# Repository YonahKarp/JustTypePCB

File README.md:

PCB for the first prototype of the JustType Leaf [JustTypeLeaf.com](https://justtypeleaf.com/)

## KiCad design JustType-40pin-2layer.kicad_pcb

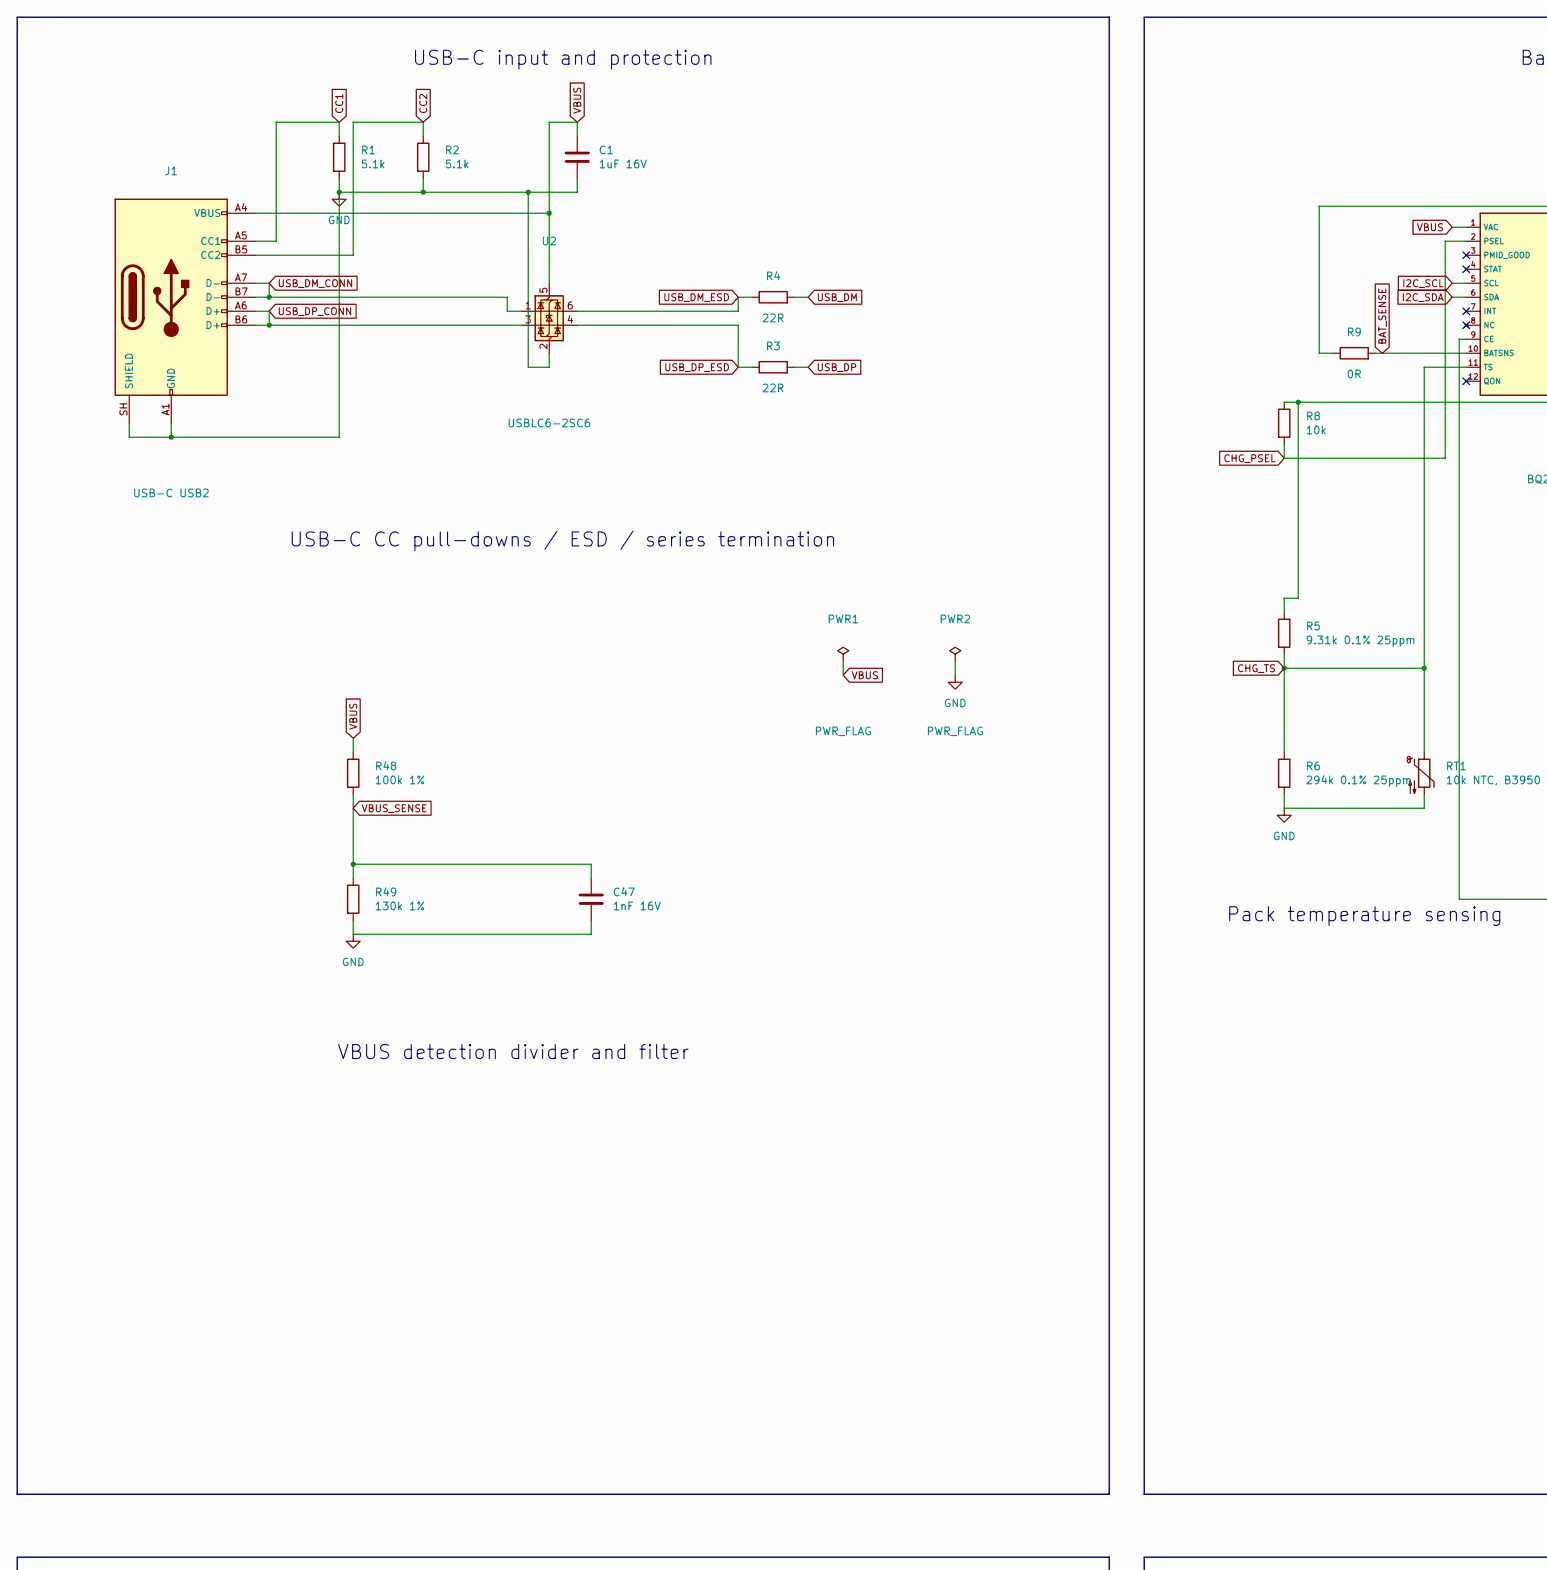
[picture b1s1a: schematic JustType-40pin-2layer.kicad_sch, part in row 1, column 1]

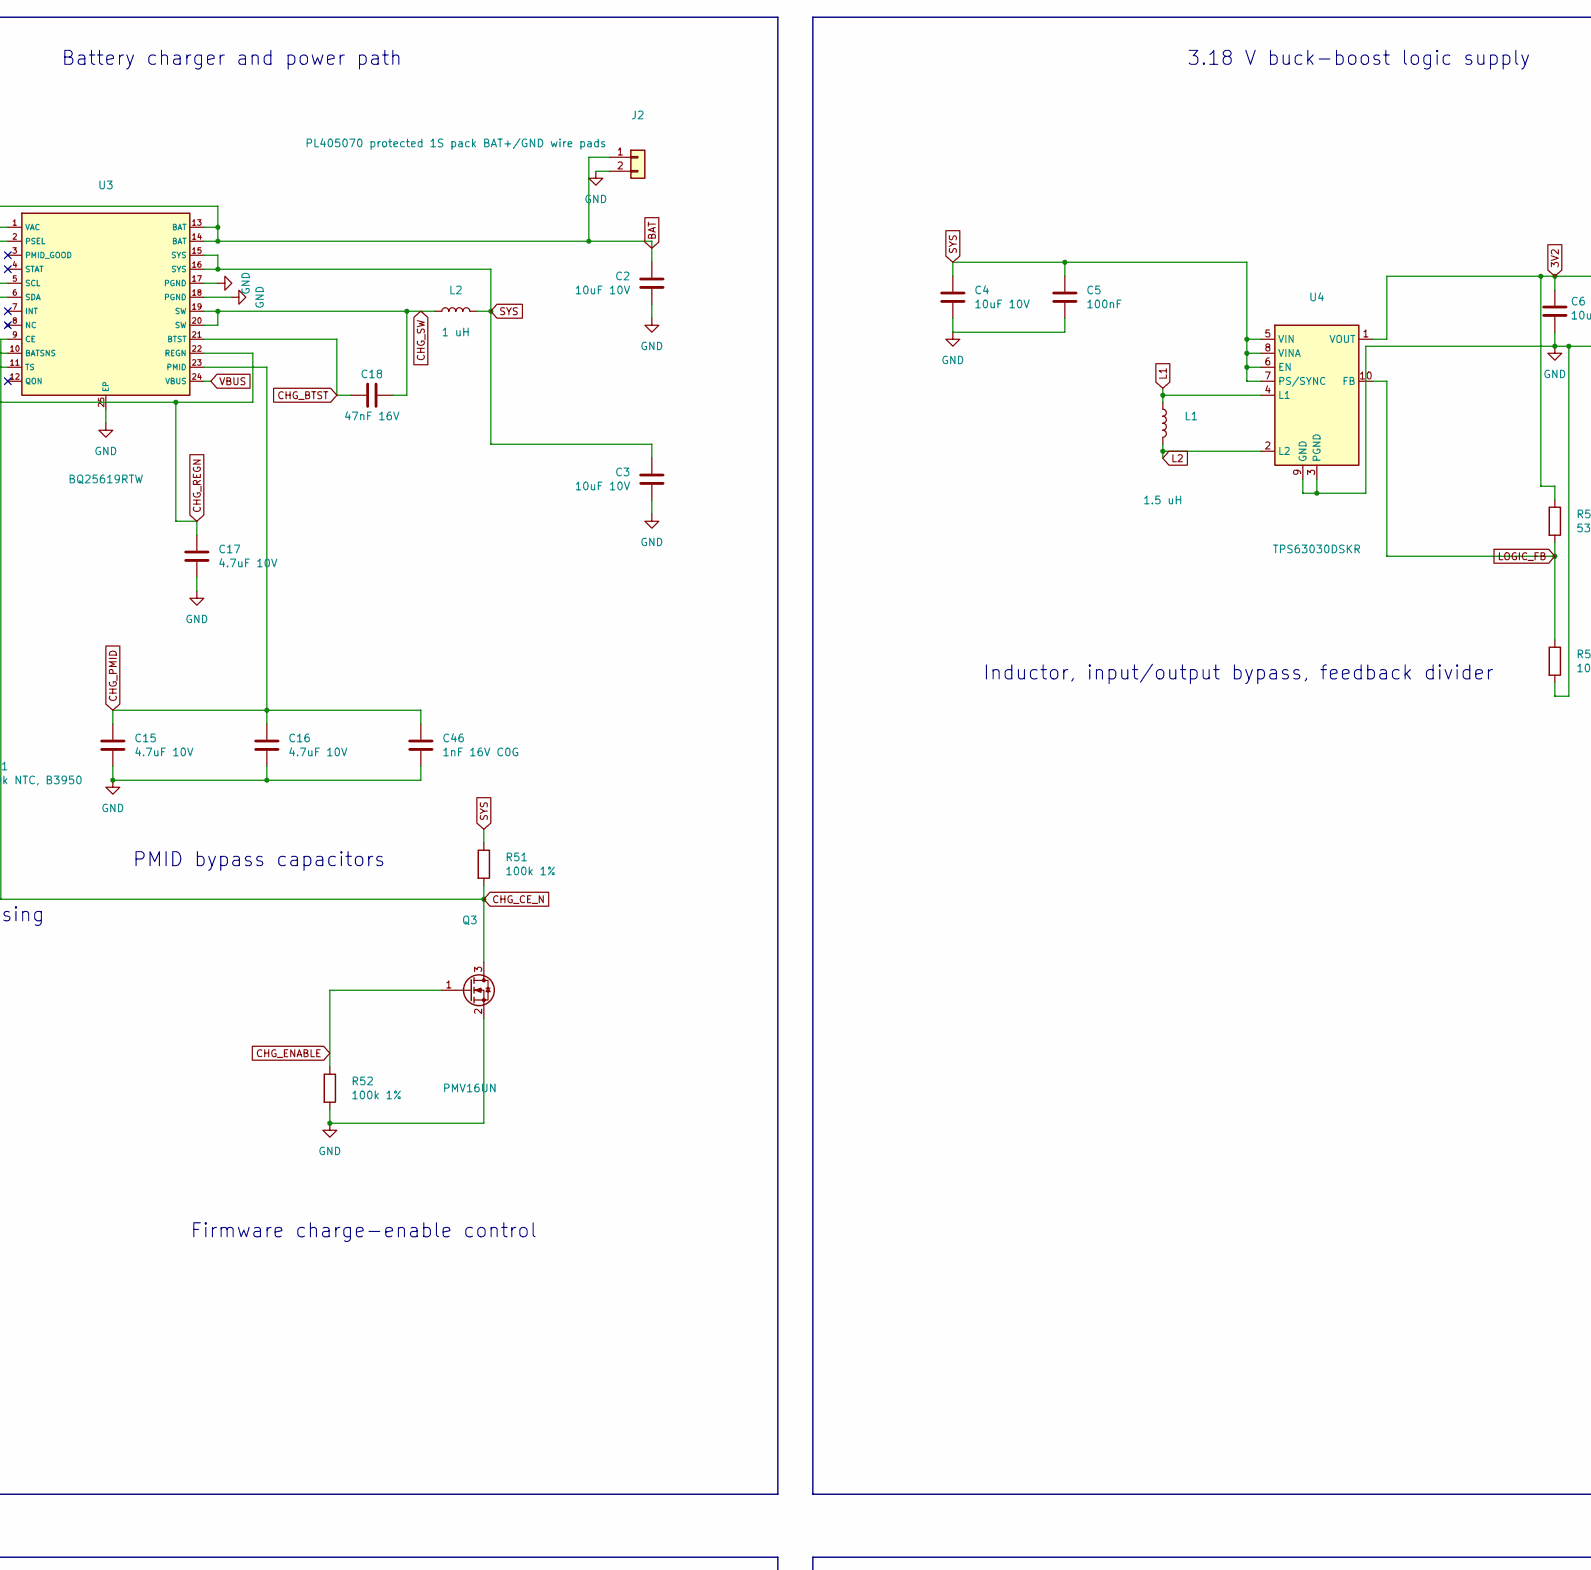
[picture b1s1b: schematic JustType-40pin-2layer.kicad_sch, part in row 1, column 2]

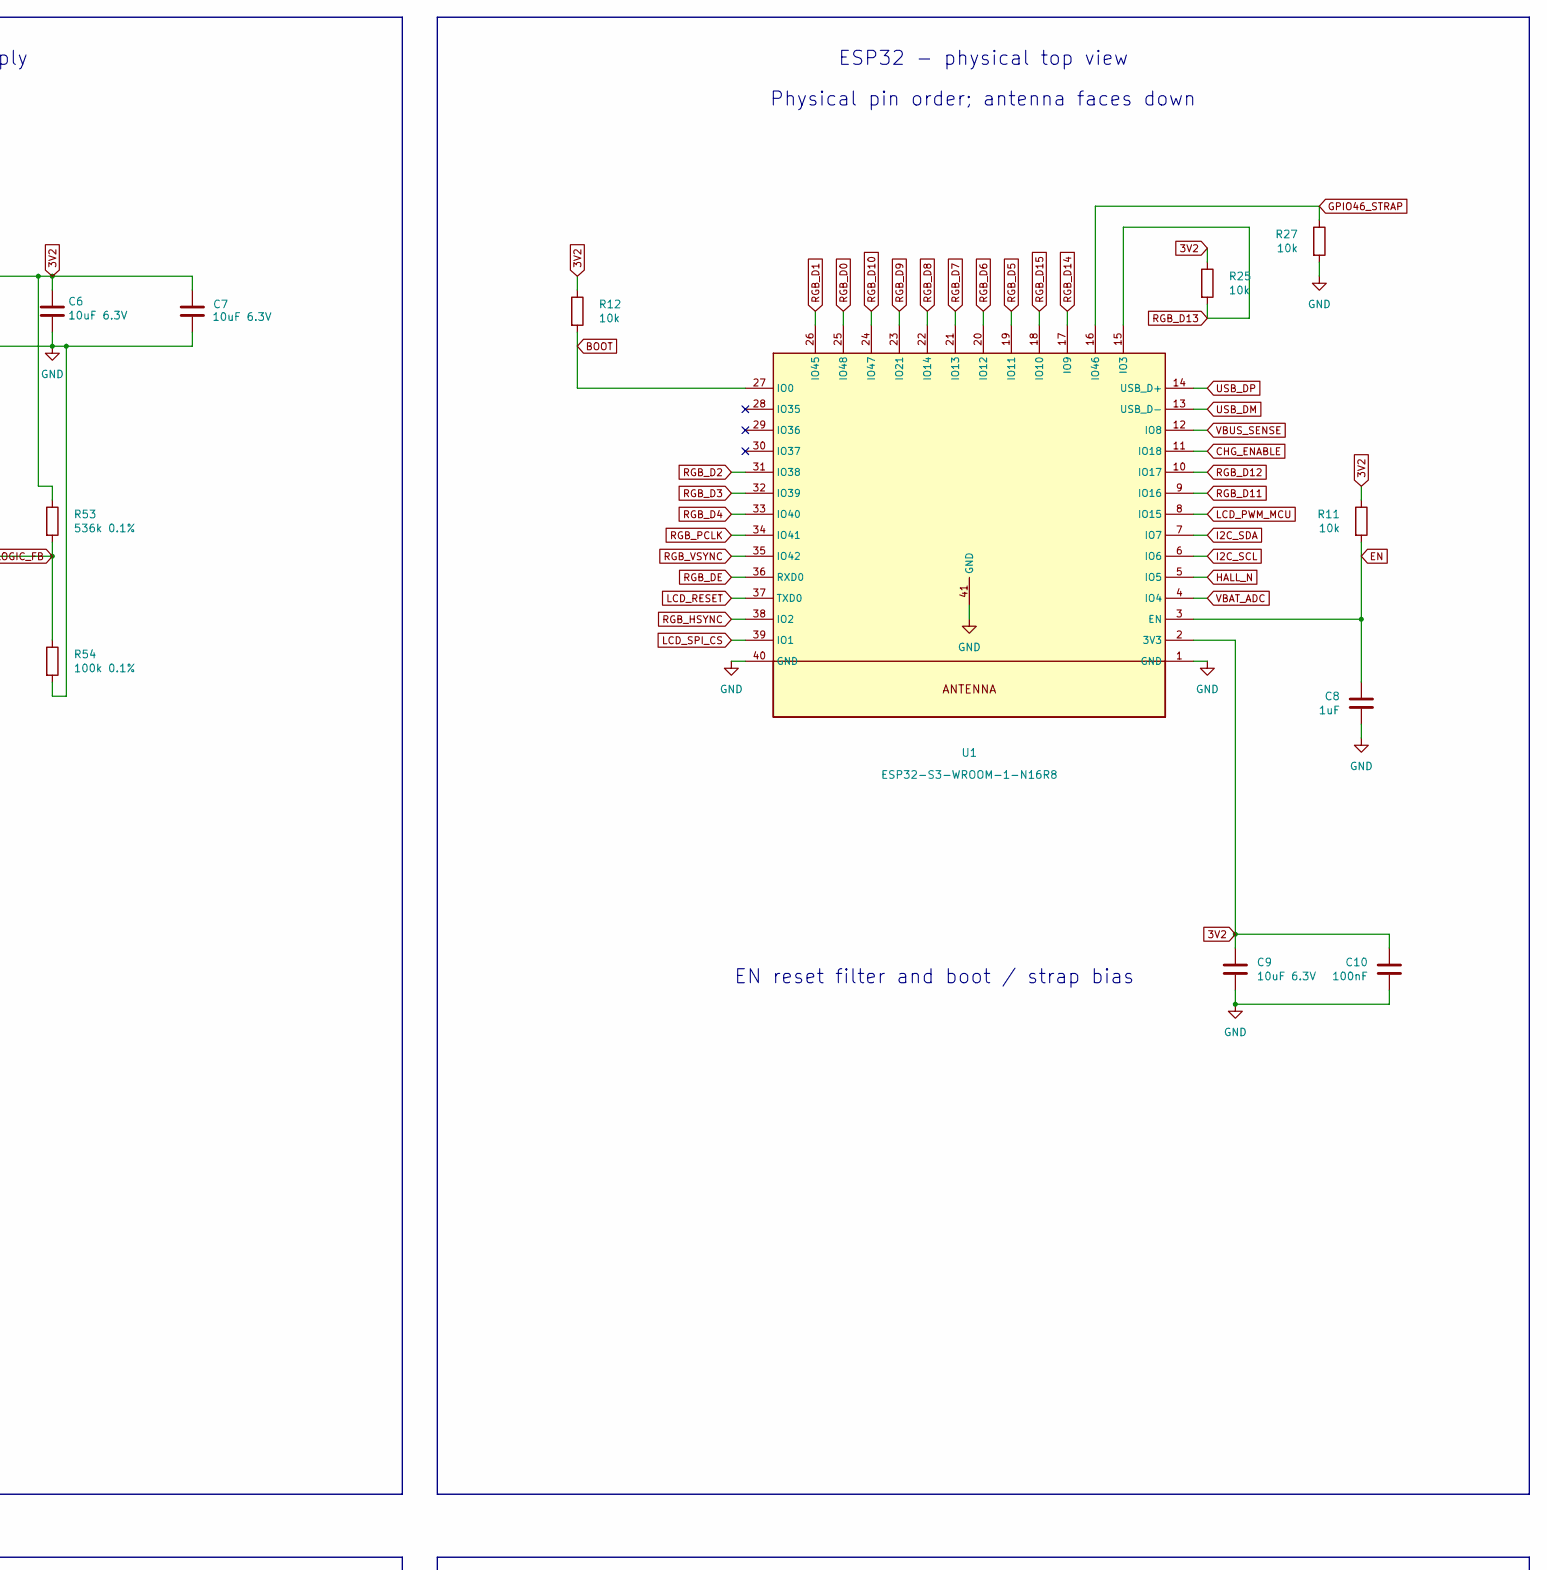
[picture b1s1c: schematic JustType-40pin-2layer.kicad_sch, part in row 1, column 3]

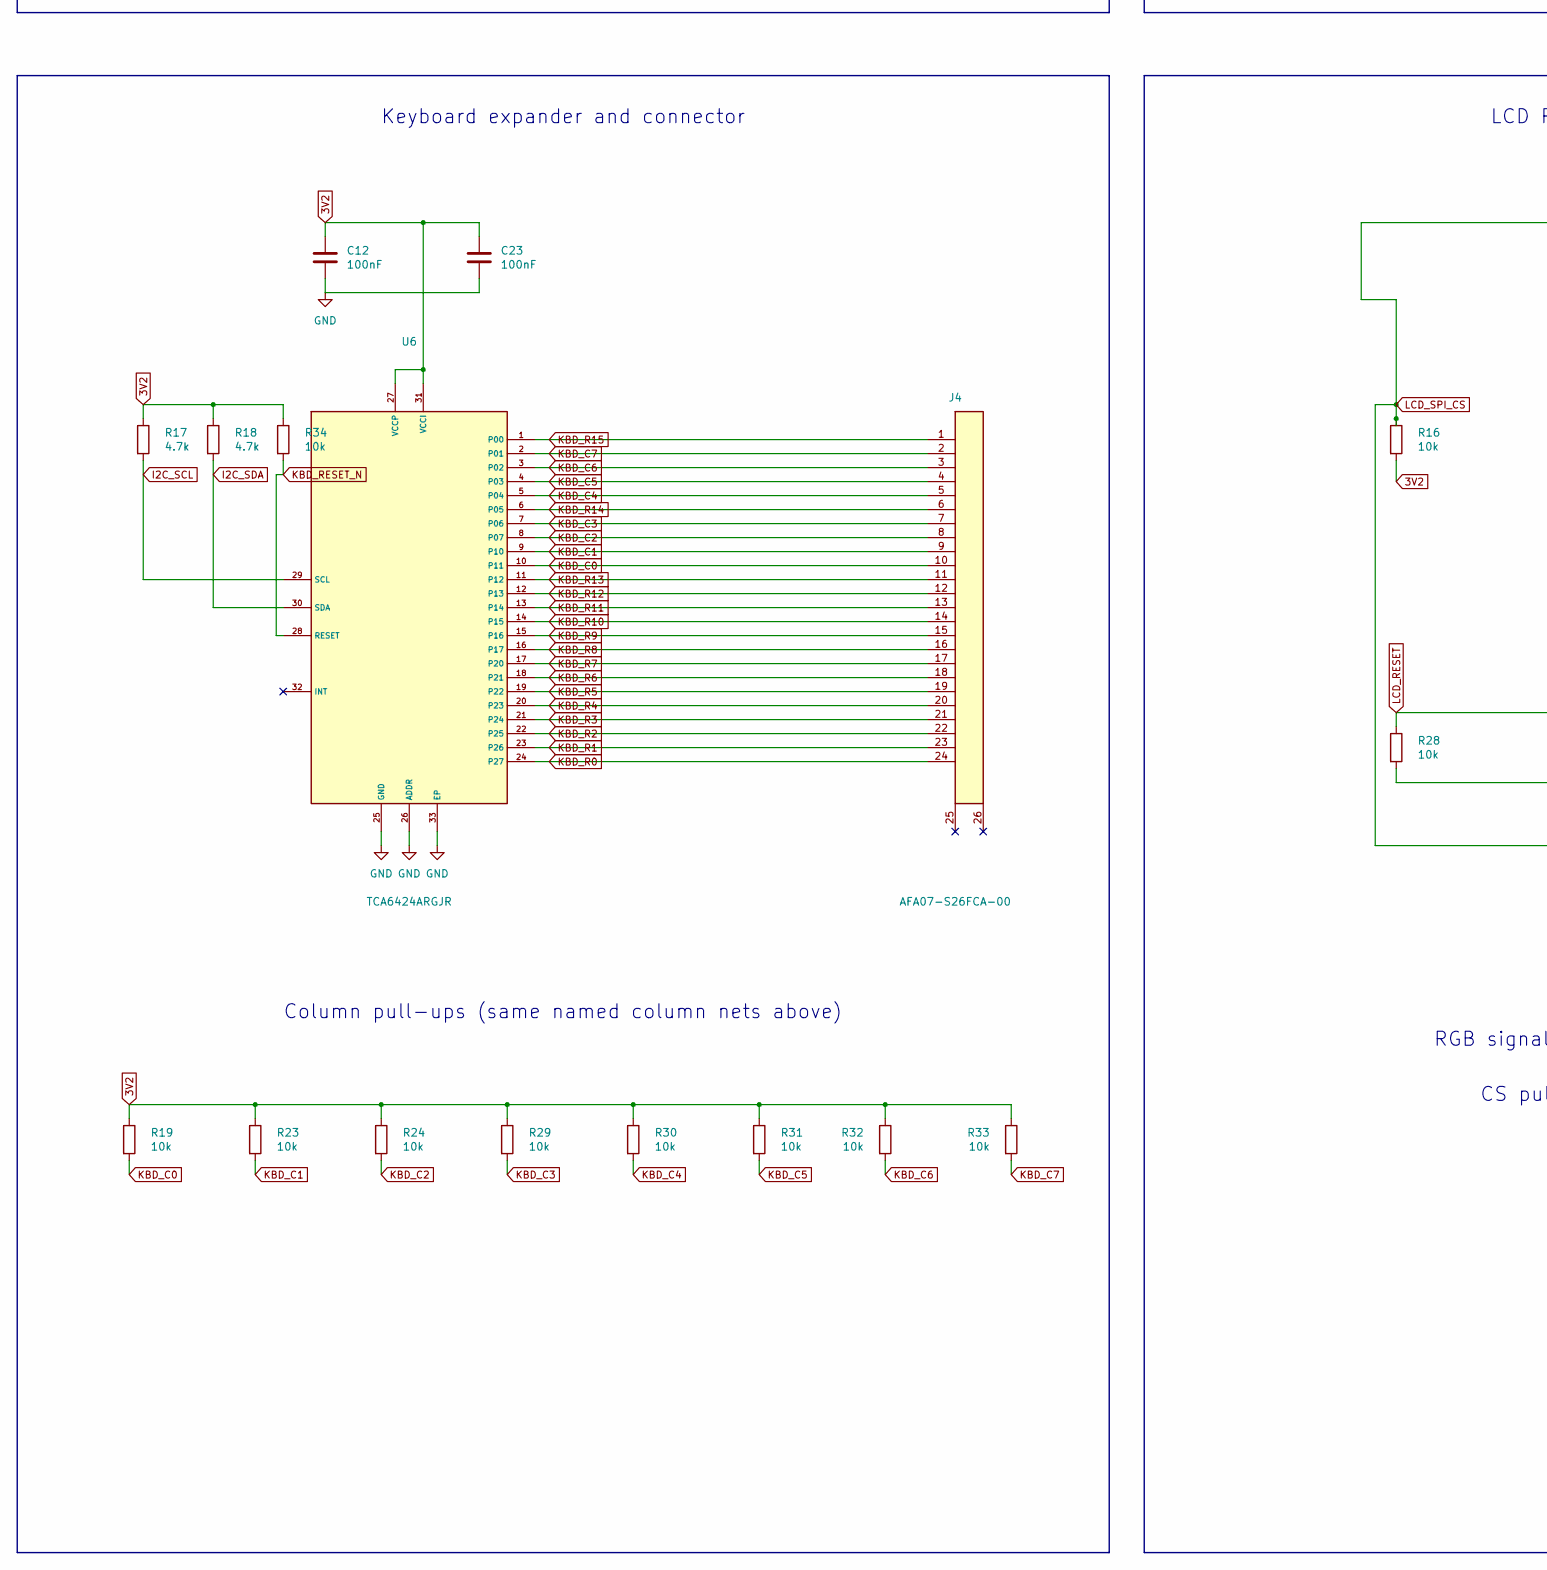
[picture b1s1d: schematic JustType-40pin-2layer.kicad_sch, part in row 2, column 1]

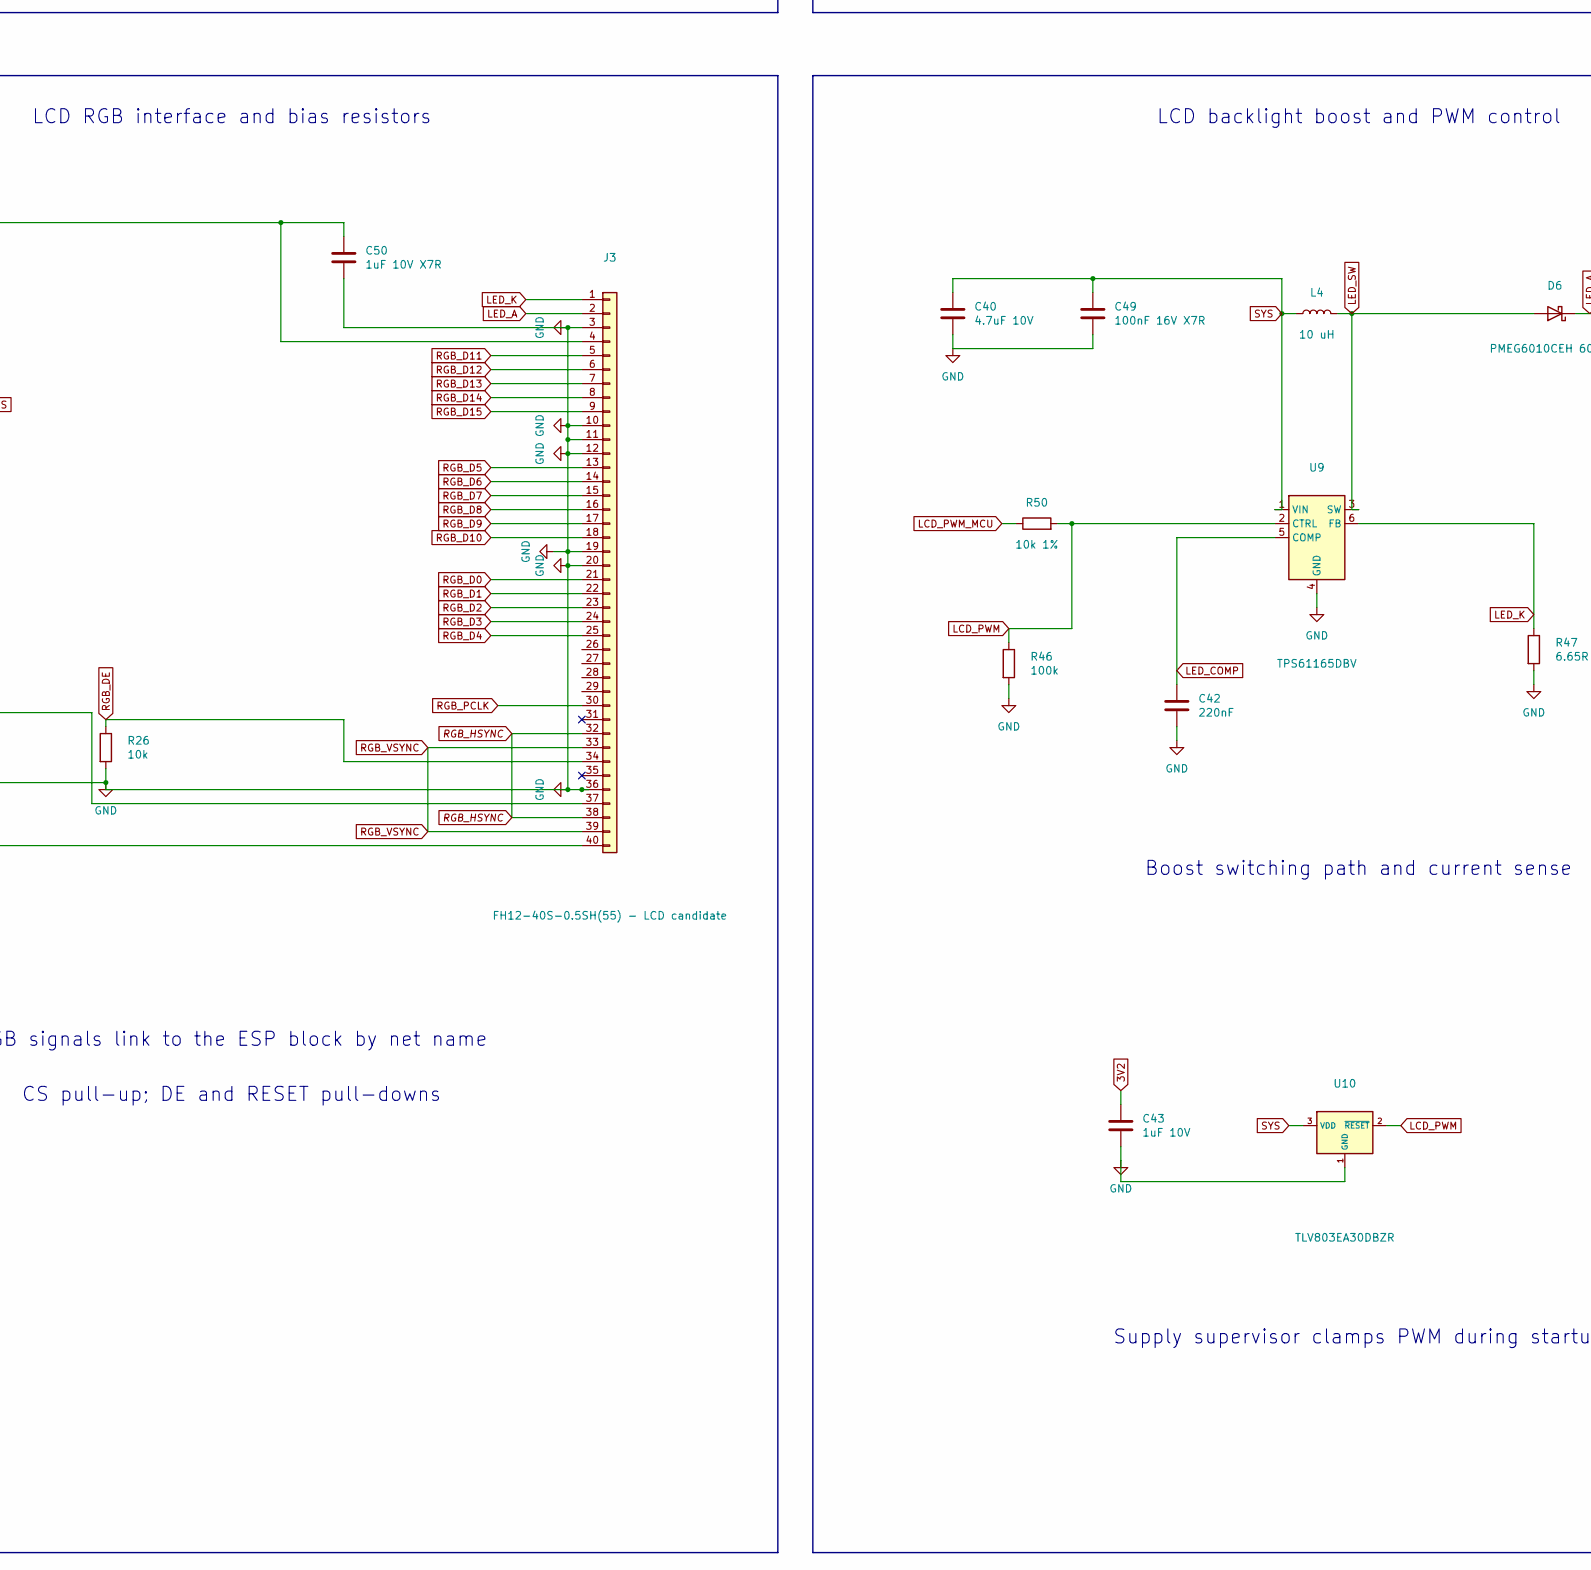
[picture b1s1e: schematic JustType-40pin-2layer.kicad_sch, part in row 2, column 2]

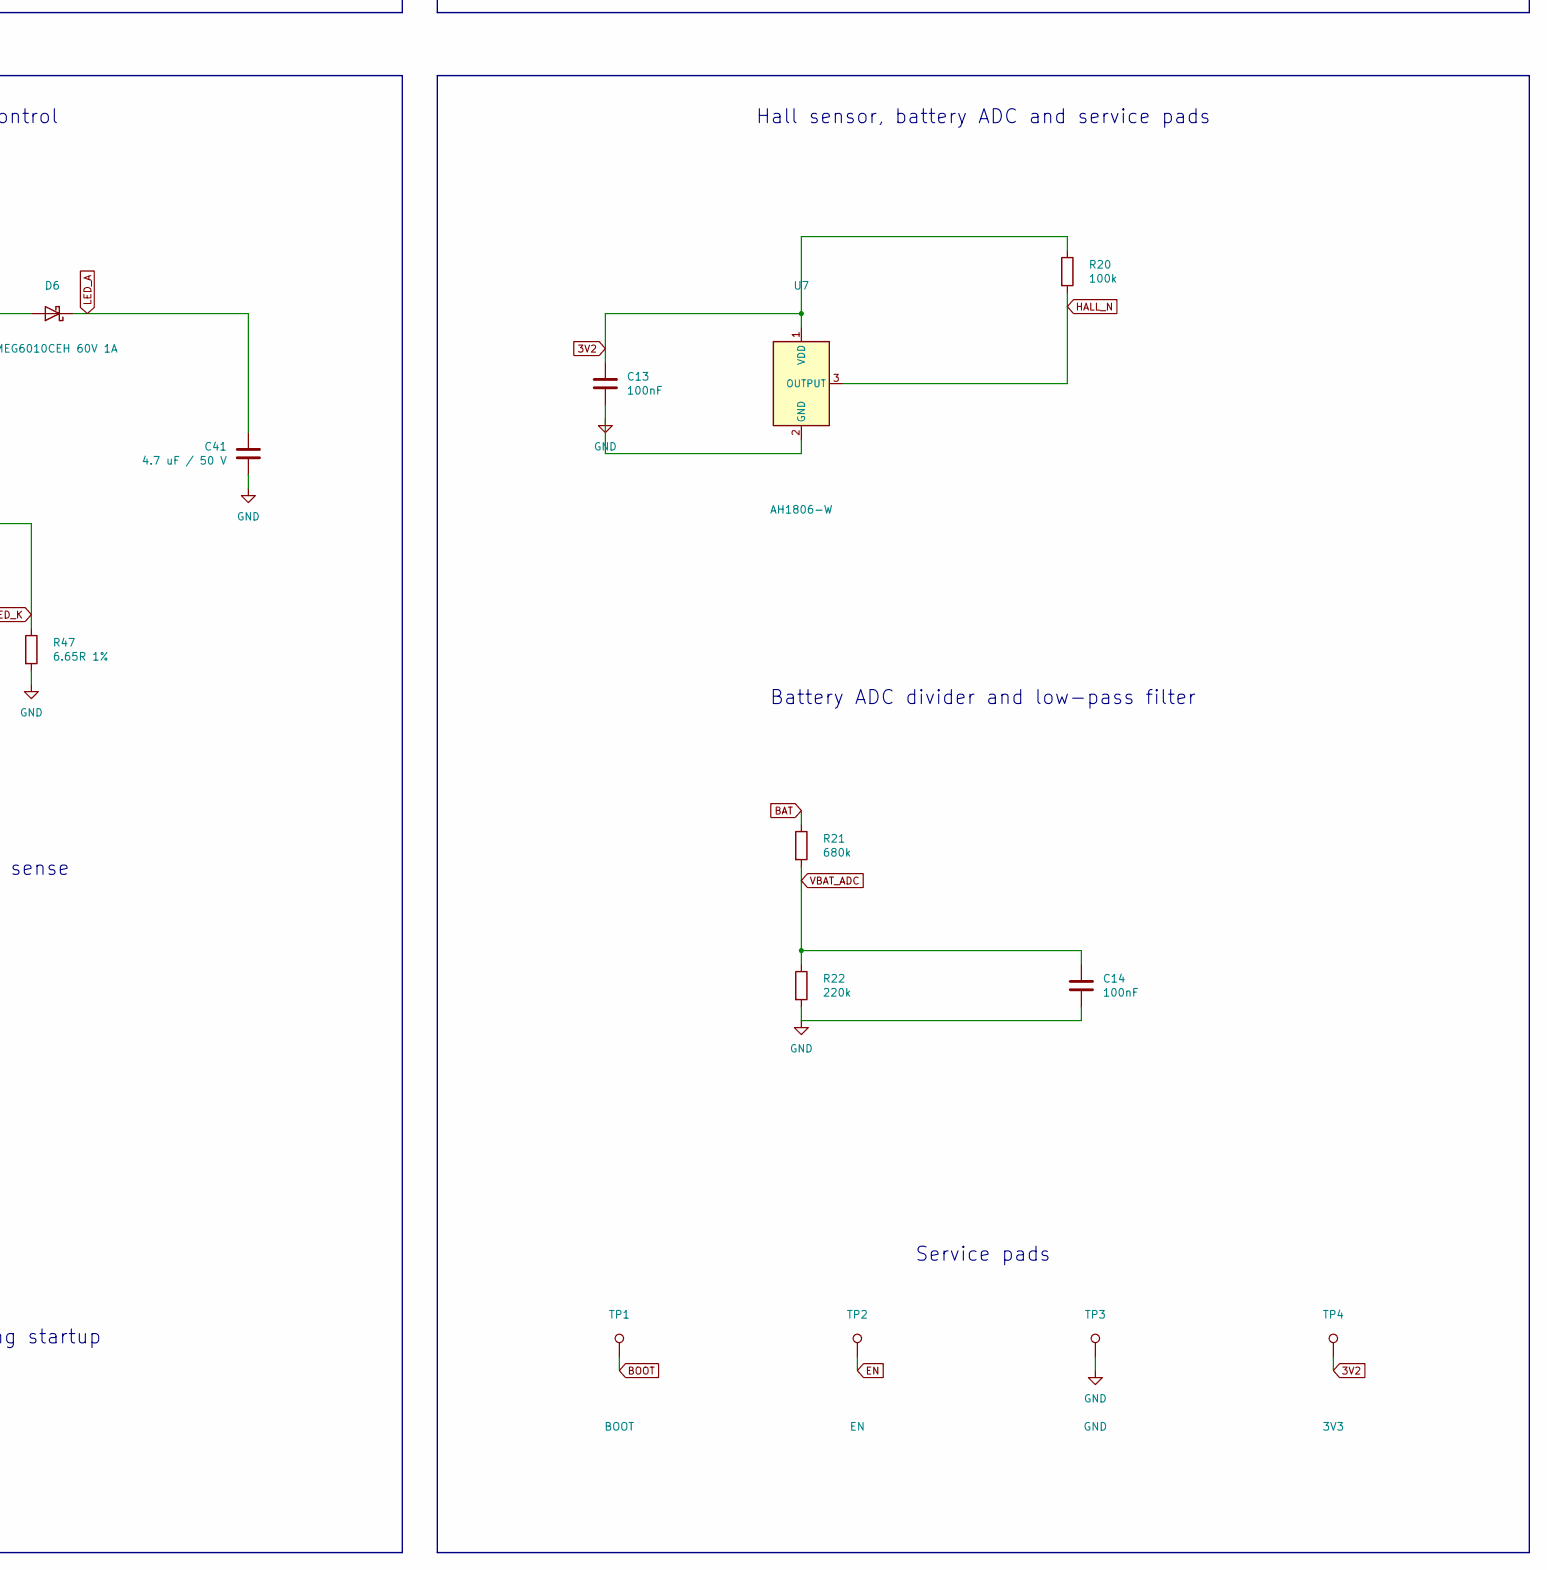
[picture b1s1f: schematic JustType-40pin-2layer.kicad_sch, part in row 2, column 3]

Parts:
C1: 1uF 16V; C_0402_1005Metric
C2, C3, C4: 10uF 10V; C_0805_2012Metric
C5, C10, C12, C13, C14, C23: 100nF; C_0603_1608Metric
C6, C7: 10uF 6.3V; C_0805_2012Metric
C8: 1uF; C_0603_1608Metric
C9: 10uF 6.3V; C_0603_1608Metric
C15, C16, C17, C40: 4.7uF 10V; C_0805_2012Metric
C18: 47nF 16V; C_0402_1005Metric
C41: 4.7uF 50V X7R GRM32ER71H475KA88K; C_1210_3225Metric
C42: 220nF; C_0603_1608Metric
C43: 1uF 10V; C_0603_1608Metric
C46: 1nF 16V C0G; C_0603_1608Metric
C47: 1nF 16V; C_0603_1608Metric
C49: 100nF 16V X7R; C_0402_1005Metric
C50: 1uF 10V X7R; C_0603_1608Metric
D6: PMEG6010CEH 60V 1A; D_SOD-123F
J1: USB-C USB2; USB_C_Receptacle_HRO_TYPE-C-31-M-12_Edge
J2: PL405070 protected 1S pack BAT+/GND wire pads; Battery_Wire_Solder_Pads
J3: FH12-40S-0.5SH(55) - LCD candidate; Hirose_FH12-40S-0.5SH_1x40-1MP_P0.50mm_Horizontal
J4: AFA07-S26FCA-00; JUSHUO_AFA07-S26FCA-00_1x26_P1.00mm_Horizontal
L1: SWPA3015S1R5NT 1.5uH; L_Sunlord_SWPA3015S
L2: SWPA3015S1R0NT 1uH; L_Sunlord_SWPA3015S
L4: SWPA4030S100MT 10uH; L_Sunlord_SWPA4030S
PWR1, PWR2: PWR_FLAG
Q3: PMV16UN; SOT-23
R1, R2: 5.1k; R_0603_1608Metric
R3, R4: 22R; R_0603_1608Metric
R5: 9.31k 0.1% 25ppm; R_0603_1608Metric
R6: 294k 0.1% 25ppm; R_0603_1608Metric
R8, R11, R12, R16, R19, R23, R24, R25, R26, R27, R28, R29, R30, R31, R32, R33, R34: 10k; R_0603_1608Metric
R9: 0R; R_0603_1608Metric
R17, R18: 4.7k; R_0603_1608Metric
R20, R46: 100k; R_0603_1608Metric
R21: 680k; R_0603_1608Metric
R22: 220k; R_0603_1608Metric
R47: 6.65R 1%; R_0603_1608Metric
R48, R51, R52: 100k 1%; R_0603_1608Metric
R49: 130k 1%; R_0603_1608Metric
R50: 10k 1%; R_0603_1608Metric
R53: 536k 0.1%; R_0603_1608Metric
R54: 100k 0.1%; R_0603_1608Metric
RT1: 10k NTC B3950 pack thermistor pads; Remote_NTC_Wire_Pads
TP1: BOOT; ServiceProbe_1mm_TP1
TP2: EN; ServiceProbe_1mm_TP2
TP3: GND; TestPoint_Pad_D1.5mm
TP4: 3V3; TestPoint_Pad_D1.5mm
U1: ESP32-S3-WROOM-1-N16R8; ESP32-S3-WROOM-1-NoRF
U2: USBLC6-2SC6; SOT-23-6
U3: BQ25619RTW; Texas_RTW_WQFN-24-1EP_4x4mm_P0.5mm_EP2.7x2.7mm
U4: TPS63030DSKR; WSON-10-1EP_2.5x2.5mm_P0.5mm_EP1.2x2mm
U6: TCA6424ARGJR; Texas_RGJ0032A_UQFN-32-1EP_5x5mm_P0.5mm_EP3.15x3.15mm
U7: AH1806-W; SC-59
U9: TPS61165DBV; SOT-23-6
U10: TLV803EA30DBZR; SOT-23

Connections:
BAT: C2.1, J2.1, R9.1, R21.1, U3.13 (BAT), U3.14 (BAT)
BAT_SENSE: R9.2, U3.10 (BATSNS)
BOOT: R12.2, TP1.1, U1.27 (IO0)
CC1: J1.A5 (CC1), R1.1
CC2: J1.B5 (CC2), R2.1
CHG_BTST: C18.1, U3.21 (BTST)
CHG_CE_N: Q3.3 (D), R51.2, U3.9 (CE)
CHG_ENABLE: Q3.1 (G), R52.1, U1.11 (IO18)
CHG_PMID: C15.1, C16.1, C46.1, U3.23 (PMID)
CHG_PSEL: R8.2, U3.2 (PSEL)
CHG_REGN: C17.1, R5.1, R8.1, U3.22 (REGN)
CHG_SW: C18.2, L2.1, U3.19 (SW), U3.20 (SW)
CHG_TS: R5.2, R6.1, RT1.1, U3.11 (TS)
EN: C8.1, R11.2, TP2.1, U1.3 (EN)
GND: C1.2, C2.2, C3.2, C4.2, C5.2, C6.2, C7.2, C8.2, C9.2, C10.2, C12.2, C13.2, C14.2, C15.2, C16.2, C17.2, C23.2, C40.2, C41.2, C42.2, C43.2, C46.2, C47.2, C49.2, C50.2, J1.A1 (GND), J1.A12 (GND), J1.B1 (GND), J1.B12 (GND), J1.SH (SHIELD), J2.2, J3.3, J3.10, J3.11, J3.12, J3.19, J3.20, J3.26, J3.27, J3.28, J3.29, J3.36, PWR2.1, Q3.2 (S), R1.2, R2.2, R6.2, R22.2, R26.2, R27.2, R28.2, R46.2, R47.2, R49.2, R52.2, R54.2, RT1.2, TP3.1, U1.1 (GND), U1.40 (GND), U1.41 (GND), U2.2 (GND), U3.17 (PGND), U3.18 (PGND), U3.25 (EP), U4.3 (PGND), U4.9 (GND), U4.11 (PGND), U6.25 (GND), U6.26 (ADDR), U6.33 (EP), U7.2 (GND), U9.4 (GND), U10.1 (GND)
GPIO46_STRAP: R27.1, U1.16 (IO46)
HALL_N: R20.2, U1.5 (IO5), U7.3 (OUTPUT)
I2C_SCL: R17.2, U1.6 (IO6), U3.5 (SCL), U6.29 (SCL)
I2C_SDA: R18.2, U1.7 (IO7), U3.6 (SDA), U6.30 (SDA)
KBD_C0: J4.10, R19.2, U6.10 (P11)
KBD_C1: J4.9, R23.2, U6.9 (P10)
KBD_C2: J4.8, R24.2, U6.8 (P07)
KBD_C3: J4.7, R29.2, U6.7 (P06)
KBD_C4: J4.5, R30.2, U6.5 (P04)
KBD_C5: J4.4, R31.2, U6.4 (P03)
KBD_C6: J4.3, R32.2, U6.3 (P02)
KBD_C7: J4.2, R33.2, U6.2 (P01)
KBD_R0: J4.24, U6.24 (P27)
KBD_R1: J4.23, U6.23 (P26)
KBD_R2: J4.22, U6.22 (P25)
KBD_R3: J4.21, U6.21 (P24)
KBD_R4: J4.20, U6.20 (P23)
KBD_R5: J4.19, U6.19 (P22)
KBD_R6: J4.18, U6.18 (P21)
KBD_R7: J4.17, U6.17 (P20)
KBD_R8: J4.16, U6.16 (P17)
KBD_R9: J4.15, U6.15 (P16)
KBD_R10: J4.14, U6.14 (P15)
KBD_R11: J4.13, U6.13 (P14)
KBD_R12: J4.12, U6.12 (P13)
KBD_R13: J4.11, U6.11 (P12)
KBD_R14: J4.6, U6.6 (P05)
KBD_R15: J4.1, U6.1 (P00)
KBD_RESET_N: R34.2, U6.28 (RESET)
L1: L1.1, U4.4 (L1)
L2: L1.2, U4.2 (L2)
LCD_PWM: R46.1, R50.2, U9.2 (CTRL), U10.2 (~RESET)
LCD_PWM_MCU: R50.1, U1.8 (IO15)
LCD_RESET: J3.37, R28.1, U1.37 (TXD0)
LED_A: C41.1, D6.1 (K), J3.2
LED_COMP: C42.1, U9.5 (COMP)
LED_K: J3.1, R47.1, U9.6 (FB)
LED_SW: D6.2 (A), L4.2, U9.3 (SW)
LOGIC_FB: R53.2, R54.1, U4.10 (FB)
RGB_D0: J3.21, U1.25 (IO48)
RGB_D1: J3.22, U1.26 (IO45)
RGB_D2: J3.23, U1.31 (IO38)
RGB_D3: J3.24, U1.32 (IO39)
RGB_D4: J3.25, U1.33 (IO40)
RGB_D5: J3.13, U1.19 (IO11)
RGB_D6: J3.14, U1.20 (IO12)
RGB_D7: J3.15, U1.21 (IO13)
RGB_D8: J3.16, U1.22 (IO14)
RGB_D9: J3.17, U1.23 (IO21)
RGB_D10: J3.18, U1.24 (IO47)
RGB_D11: J3.5, U1.9 (IO16)
RGB_D12: J3.6, U1.10 (IO17)
RGB_D13: J3.7, R25.2, U1.15 (IO3)
RGB_D14: J3.8, U1.17 (IO9)
RGB_D15: J3.9, U1.18 (IO10)
RGB_DE: J3.34, R26.1, U1.36 (RXD0)
RGB_HSYNC: J3.32, J3.38, U1.38 (IO2)
RGB_PCLK: J3.30, U1.34 (IO41)
RGB_VSYNC: J3.33, J3.39, U1.35 (IO42)
SYS: C3.1, C4.1, C5.1, C40.1, C49.1, L2.2, L4.1, R51.1, U3.15 (SYS), U3.16 (SYS), U4.5 (VIN), U4.6 (EN), U4.7 (PS/SYNC), U4.8 (VINA), U9.1 (VIN), U10.3 (VDD)
USB_DM: R4.2, U1.13 (USB_D-)
USB_DM_CONN: J1.A7 (D-), J1.B7 (D-), U2.1 (I/O1)
USB_DM_ESD: R4.1, U2.6 (I/O1)
USB_DP: R3.2, U1.14 (USB_D+)
USB_DP_CONN: J1.A6 (D+), J1.B6 (D+), U2.3 (I/O2)
USB_DP_ESD: R3.1, U2.4 (I/O2)
VBAT_ADC: C14.1, R21.2, R22.1, U1.4 (IO4)
VBUS: C1.1, J1.A4 (VBUS), J1.A9 (VBUS), J1.B4 (VBUS), J1.B9 (VBUS), PWR1.1, R48.1, U2.5 (VBUS), U3.1 (VAC), U3.24 (VBUS)
VBUS_SENSE: C47.1, R48.2, R49.1, U1.12 (IO8)

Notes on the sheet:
Battery ADC divider and low-pass filter
Physical pin order; antenna faces down
USB-C CC pull-downs / ESD / series termination
PMID bypass capacitors
Inductor, input/output bypass, feedback divider
Pack temperature sensing
3.18 V buck-boost logic supply
VBUS detection divider and filter
Battery charger and power path
Supply supervisor clamps PWM during startup
Boost switching path and current sense
Keyboard expander and connector
LCD RGB interface and bias resistors
USB-C input and protection
RGB signals link to the ESP block by net name
Column pull-ups (same named column nets above)
EN reset filter and boot / strap bias
LCD backlight boost and PWM control
ESP32 - physical top view
CS pull-up; DE and RESET pull-downs
Firmware charge-enable control
Service pads
Hall sensor, battery ADC and service pads

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
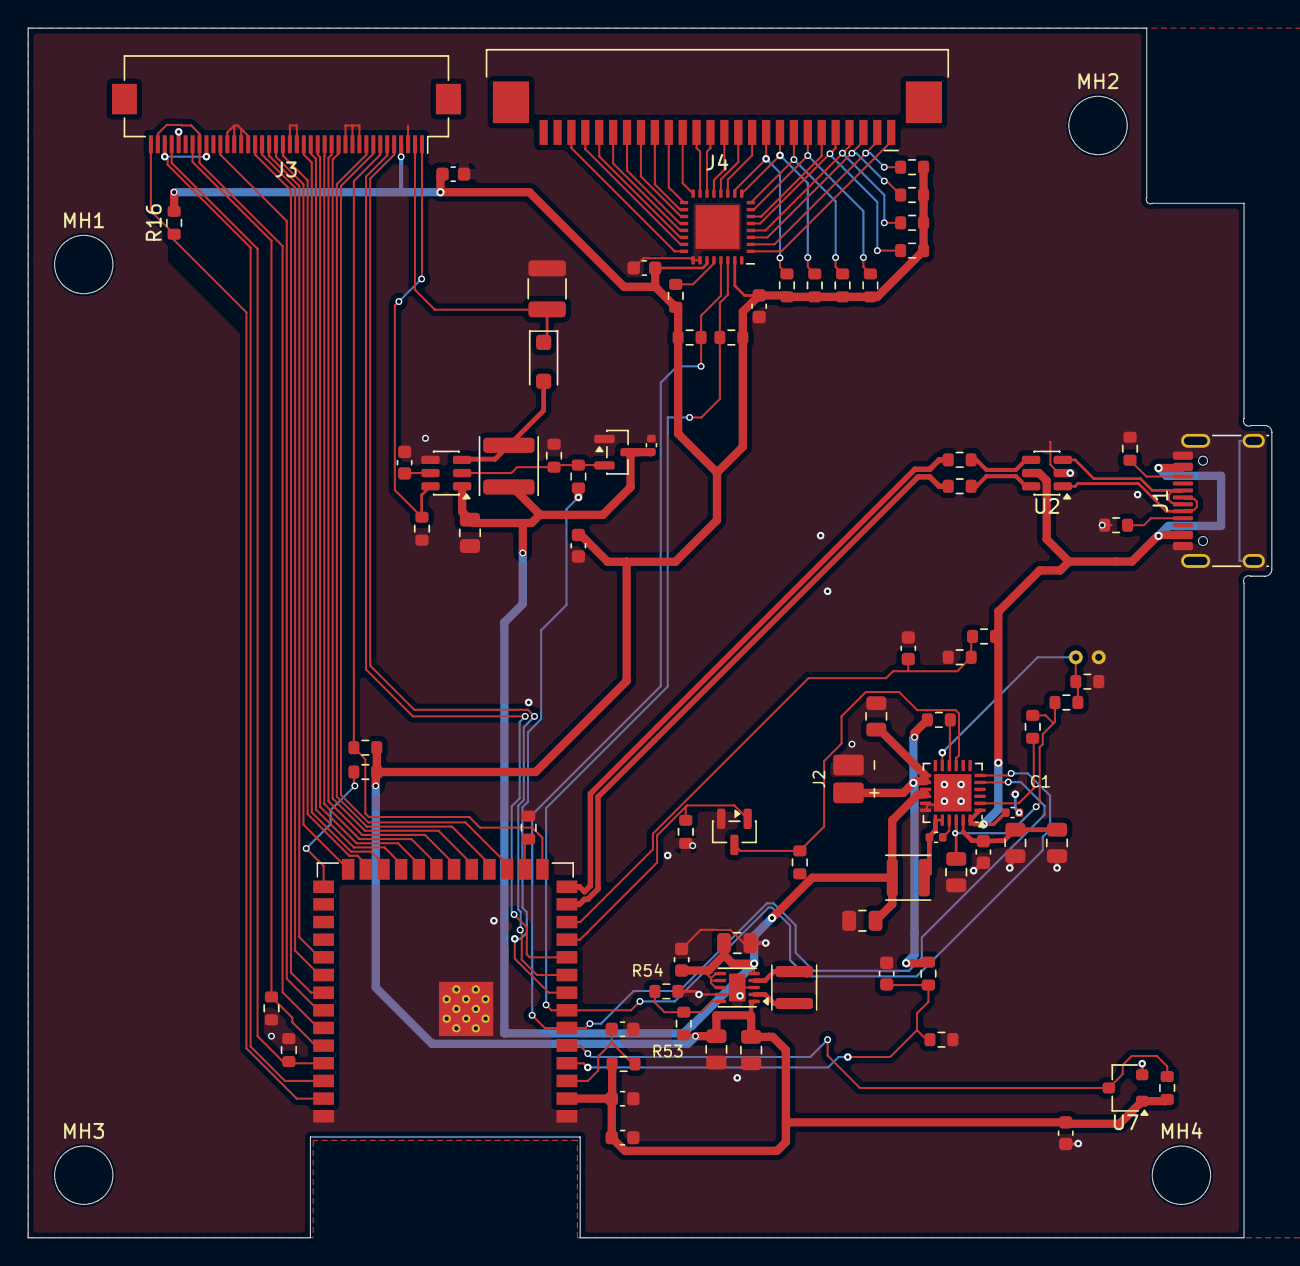
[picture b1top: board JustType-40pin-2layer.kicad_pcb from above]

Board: 2 copper layers, 89.4 x 87.0 mm, 86 parts (0 on the bottom side), 86 nets.

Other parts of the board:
MH1, MH2, MH3, MH4: MountingHole_4.2mm_PostClearance
